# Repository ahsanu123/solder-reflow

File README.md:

<h1 align="center">🌕 SORE V3 - Prototype 1</h1> 
<p align="center">
  
</p>

<p align="center">

</p>

## ✏️ SORE - Solder Reflow

🌕 SORE - Solder Reflow,  DIY hot plate use PT100 for temperature sensor controlled with ESP32-S3,
with TFT LCD, programmed in 🦀 Rust with [Slint](https://slint.dev/) as user interface

> Designed With [KICAD](https://www.kicad.org)

## 🏆 WIP For Version 3

> [!NOTE]
> - use esp32-s3
> - use usb jtag and usb serial 
> - try to use power supply module instead of using external adaptor, [Hi-Link](https://www.tokopedia.com/eltech-online/hi-link-3-3v-5v-9v-12v-24v-hi-link-ling-hlk-ac-to-dc-isolation-power-supply-unit-switching-module-catu-daya-adaptor-trafo-all-1731008119444047082?extParam=ivf%3Dfalse%26keyword%3Dpower+supply+ac+dc%26search_id%3D20250611123128432ACA3A1E345E32EJ1R%26src%3Dsearch)
> - add generic lcd spi connector instead of spesific display pinout.
> - use [Slint](https://slint.dev/) for user interface
> - think about how to stack the heater so its not separated, model it with inventor
> - if possible, buy local component only

<details>
 <summary>Sketch</summary>
  
</details>
 
## 🖍️ Plot of Sampled Data

<details>
 <summary>
  Plot Collection
 </summary>
 
- multiple sampling at 2Mhz (except first one)
signal was moving averaged filter, first graph was actually noisy, and rest was actually not really noisy, but after filtered low noise signal look bumped

- Transfer Function Estimation
$`y(t) = 350(1-e^{(t-d)/tau})`$ in temperature degre (celcius), d = 17.5 second

- first time sampled diagram [30 oktober 2024]

</details>

## 🌱 V3 Project Progress

<details>
 <summary>
  Expand To See Progress.
 </summary> 
  
 **Version 2**
- PCB Design Finished 10 june 2024 20:51
- Order _BOM_ and PCB
- PCB and BOM Arrive 12 july 2024 about 16:00
- Start to soldering 13 july 2024 about 06:00 (**weekend**)
- make adc class to simplify adc initialization 23 july 2024 at 21:21
- Check Out GPIO (Worked!!😃) 26 july 2024 at 22:24
- Try to use JLink for jtag debugging, but fail 😞 , 27 july 2024 at 17:30
- Try again to use JLink for jtag debugging, Worked!! 😃 , 28 july 2024 at 11:36
- Add `Button` class to add Input with callback, 29 Agustus 2024 at 19:42
- ⚠️ turn out, TL074 (not TL074xH) need minimum 10v to operate and not single supply quad opamp 😞, fortunately there is LM324 (same package and single supply support), currently still in shipping, need to wait if it really work or not, 01 september 2024 at 18:05
- ✔️ ok LM324 worked, currently still investigate why adc are really noisy, 03 september 2024 at 13:34
- looks ESP32 IDF adc getting more stable if `frequency` increased, try to use 20Khz but its not stable, but use 1Mhz its more stable 14 september 2024 at 21:00
- ✔️ LVGL worked but task semaphore block update of LVGL (still investigate), 05 oktober 2024 at 10:13
- ✔️ now LVGL with Button input worked!! 😃, need learn more how to map LVGL key to input button, 05 oktober 2024 at 13:23
- ✔️ sampling data from heater and plot it, 30 oktober 2024 at 2015

**Version 3**
- ⏰ 11 June 2025 19:31, make it version 3,
- ⏰ 14 September 2025 12:57, complete basic pcb component placement.
- ⏰ 14 September 2025 17:59, after searching for **Random turn on SSR** (non Zero Crossing) on local market, i cant find easy to buy device, so i will stick to use zero crossing ssr and will count for zero crossing with **H11AA1** and determine how long to turn on and turn off.

- ⏰ 15 March 2026, able to run slint on ESP32S3 on `temperature-measurement-dongle`

</details>

## 🌴 Reference 

- Slint on Mcu platform sample docs -> https://github.com/slint-ui/slint/blob/master/examples/mcu-board-support/README.md
- Slint MCU support Discussion -> https://github.com/slint-ui/slint/discussions/5008
- Slint MCU Template (raspi pico) -> https://github.com/slint-ui/slint-mcu-rust-template/blob/main/src/main.rs
- Slint Linux Template (Linux, etc) -> https://github.com/slint-ui/slint-rust-template/tree/main
- Slint ESP32 Example -> https://github.com/slint-ui/slint/blob/master/examples/mcu-board-support/esp32_s3_box_3.rs
- SSR Phidgets -> https://www.phidgets.com/docs/Solid_State_Relay_Guide?srsltid=AfmBOorYCC74pJUGRt7l37kUGJY9RvW-y3PI6dPv29tLXrCDrbclxS5B

<sup> Work In Progress Version 3 for 2025 🔥, Made with ♥️ by AH... </sup>

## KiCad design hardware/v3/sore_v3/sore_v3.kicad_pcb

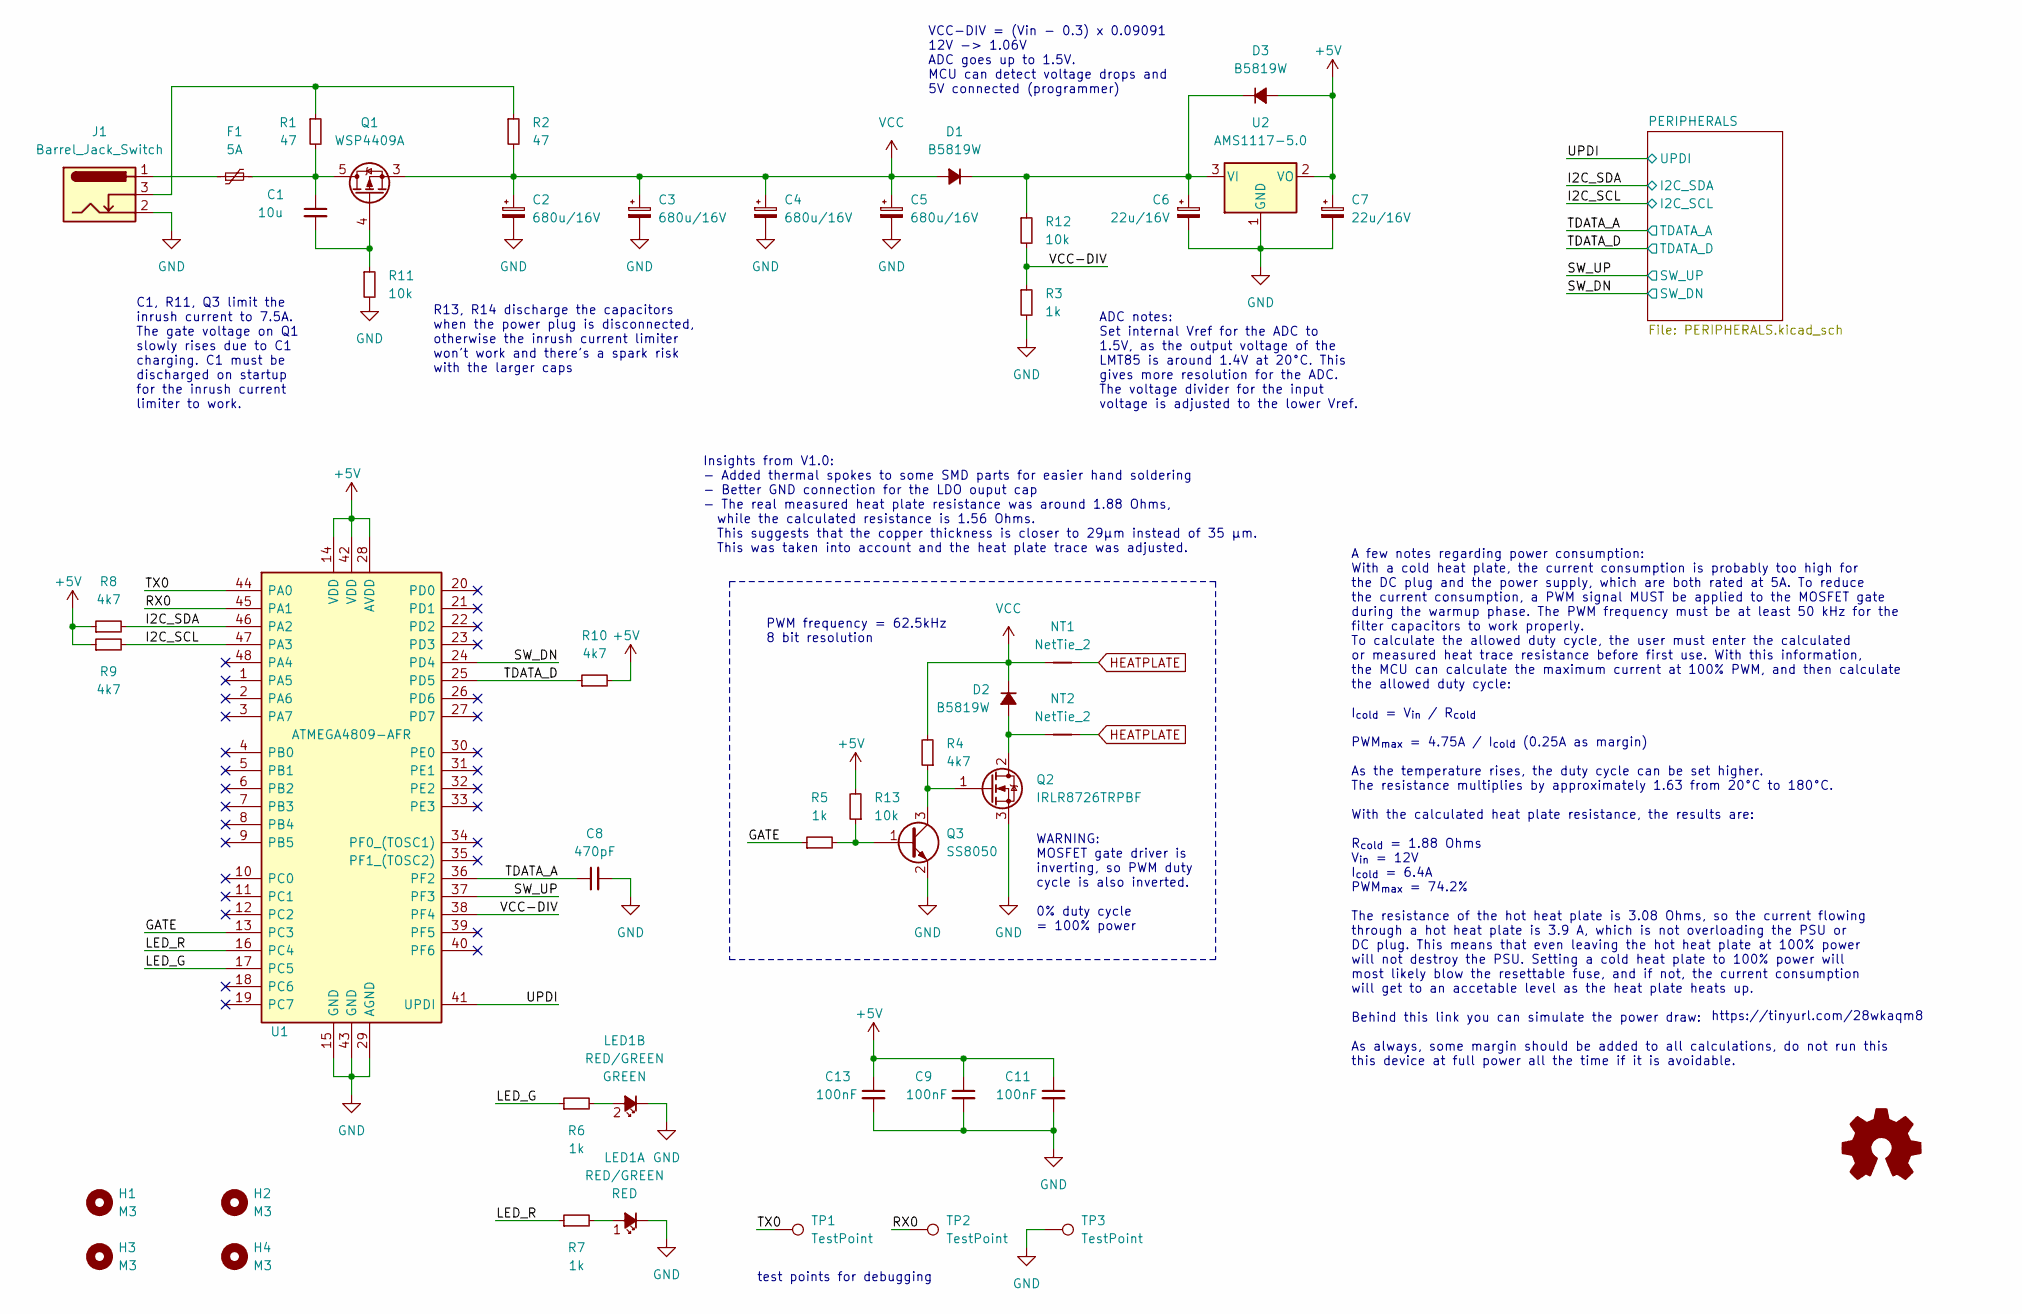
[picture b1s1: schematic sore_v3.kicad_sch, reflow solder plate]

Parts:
C1: 10u; C_0805_2012Metric; LCSC Part Number C2922480
C2, C3, C4, C5: 680u/16V; CP_Radial_D8.0mm_P3.50mm; LCSC Part Number C88760
C6, C7: 22u/16V; CP_Elec_4x5.4; LCSC Part Number C88799
C8: 470pF; C_0805_2012Metric; LCSC Part Number C1743
C9, C11, C13: 100nF; C_0805_2012Metric; LCSC Part Number C1711
D1, D2, D3: B5819W; D_SOD-123; LCSC Part Number C64885
F1: 5A; Fuse_2920_7451Metric; LCSC Part Number C910846
H1, H2, H3, H4: M3; MountingHole_3.2mm_M3; LCSC Part Number C551332
J1: Barrel_Jack_Switch; BarrelJack_Horizontal; LCSC Part Number C381115
LED1: RED/GREEN; LED_Avago_PLCC4_3.2x2.8mm_CW; LCSC Part Number C131251
LOGO1: Logo_Open_Hardware_Small; OSHW-Logo2_7.3x6mm_SilkScreen
NT1, NT2: NetTie_2; NetTie-2_SMD_Pad1.3mm
Q1: WSP4409A; SOIC-8_3.9x4.9mm_P1.27mm; LCSC Part Number C2880527
Q2: IRLR8726TRPBF; TO-252-2; LCSC Part Number C81137
Q3: SS8050; SOT-23; LCSC Part Number C444722
R1, R2: 47; R_0805_2012Metric; LCSC Part Number C17714
R3, R5, R6, R7: 1k; R_0805_2012Metric; LCSC Part Number C17513
R4, R8, R9, R10: 4k7; R_0805_2012Metric; LCSC Part Number C17673
R11, R12, R13: 10k; R_0805_2012Metric; LCSC Part Number C17414
TP1, TP2, TP3: TestPoint; TestPoint_Pad_D1.5mm
U1: ATMEGA4809-AFR; TQFP-48_7x7mm_P0.5mm; Manufacturer_Part_Number ATMEGA4809-AFR; Mouser Part Number 556-ATMEGA4809-AFR
U2: AMS1117-5.0; SOT-89-3; LCSC Part Number C351450

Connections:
+5V: C7.1, C9.1, C11.1, C13.1, D3.2 (A), R8.1, R9.1, R10.2, R13.2, U1.14 (VDD), U1.28 (AVDD), U1.42 (VDD), U2.2 (VO); also elsewhere on the board
/GATE: R5.1, U1.13 (PC3)
/I2C_SCL: R9.2, U1.47 (PA3); also elsewhere on the board
/I2C_SDA: R8.2, U1.46 (PA2); also elsewhere on the board
/LED_G: R6.1, U1.17 (PC5)
/LED_R: R7.1, U1.16 (PC4)
/RX0: TP2.1, U1.45 (PA1)
/SW_DN: U1.24 (PD4); also elsewhere on the board
/SW_UP: U1.37 (PF3); also elsewhere on the board
/TDATA_A: C8.1, U1.36 (PF2); also elsewhere on the board
/TDATA_D: R10.1, U1.25 (PD5); also elsewhere on the board
/TX0: TP1.1, U1.44 (PA0)
/UPDI: U1.41 (UPDI); also elsewhere on the board
/VCC-DIV: R3.1, R12.2, U1.38 (PF4)
GND: C2.2, C3.2, C4.2, C5.2, C6.2, C7.2, C8.2, C9.2, C11.2, C13.2, J1.2, LED1.2 (K1), LED1.4 (K2), Q2.3 (S), Q3.2 (E), R3.2, R11.2, TP3.1, U1.15 (GND), U1.29 (AGND), U1.43 (GND), U2.1 (GND); also elsewhere on the board
HEATPLATE: NT1.2, NT2.2
unnamed: C1.1, F1.2, Q1.5 (D), Q1.6 (D), Q1.7 (D), Q1.8 (D), R1.2
unnamed: C1.2, Q1.4 (G), R11.1
unnamed: C6.1, D1.1 (K), D3.1 (K), R12.1, U2.3 (VI)
unnamed: D2.2 (A), NT2.1, Q2.2 (D)
unnamed: F1.1, J1.1
unnamed: J1.3, R1.1, R2.1
unnamed: LED1.1 (A1), R7.2
unnamed: LED1.3 (A2), R6.2
unnamed: Q2.1 (G), Q3.3 (C), R4.1
unnamed: Q3.1 (B), R5.2, R13.1
VCC: C2.1, C3.1, C4.1, C5.1, D1.2 (A), D2.1 (K), NT1.1, Q1.1 (S), Q1.2 (S), Q1.3 (S), R2.2, R4.2

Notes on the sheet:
C1, R11, Q3 limit the inrush current to 7.5A. The gate voltage on Q1 slowly rises due to C1 charging. C1 must be discharged on startup for the inrush current limiter to work.
VCC-DIV = (Vin - 0.3) x 0.09091 12V -> 1.06V ADC goes up to 1.5V. MCU can detect voltage drops and 5V connected (programmer)
PWM frequency = 62.5kHz 8 bit resolution
A few notes regarding power consumption: With a cold heat plate, the current consumption is probably too high for the DC plug and the power supply, which are both rated at 5A. To reduce the current consumption, a PWM signal MUST be applied to the MOSFET gate during the warmup phase. The PWM frequen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
WARNING: MOSFET gate driver is inverting, so PWM duty cycle is also inverted. 0% duty cycle = 100% power
R13, R14 discharge the capacitors when the power plug is disconnected, otherwise the inrush current limiter won't work and there's a spark risk with the larger caps
https://tinyurl.com/28wkaqm8
test points for debugging
ADC notes: Set internal Vref for the ADC to 1.5V, as the output voltage of the LMT85 is around 1.4V at 20°C. This gives more resolution for the ADC. The voltage divider for the input voltage is adjusted to the lower Vref.
Insights from V1.0: - Added thermal spokes to some SMD parts for easier hand soldering - Better GND connection for the LDO ouput cap - The real measured heat plate resistance was around 1.88 Ohms, while the calculated resistance is 1.56 Ohms. This suggests that the copper thickness is closer to 29µ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

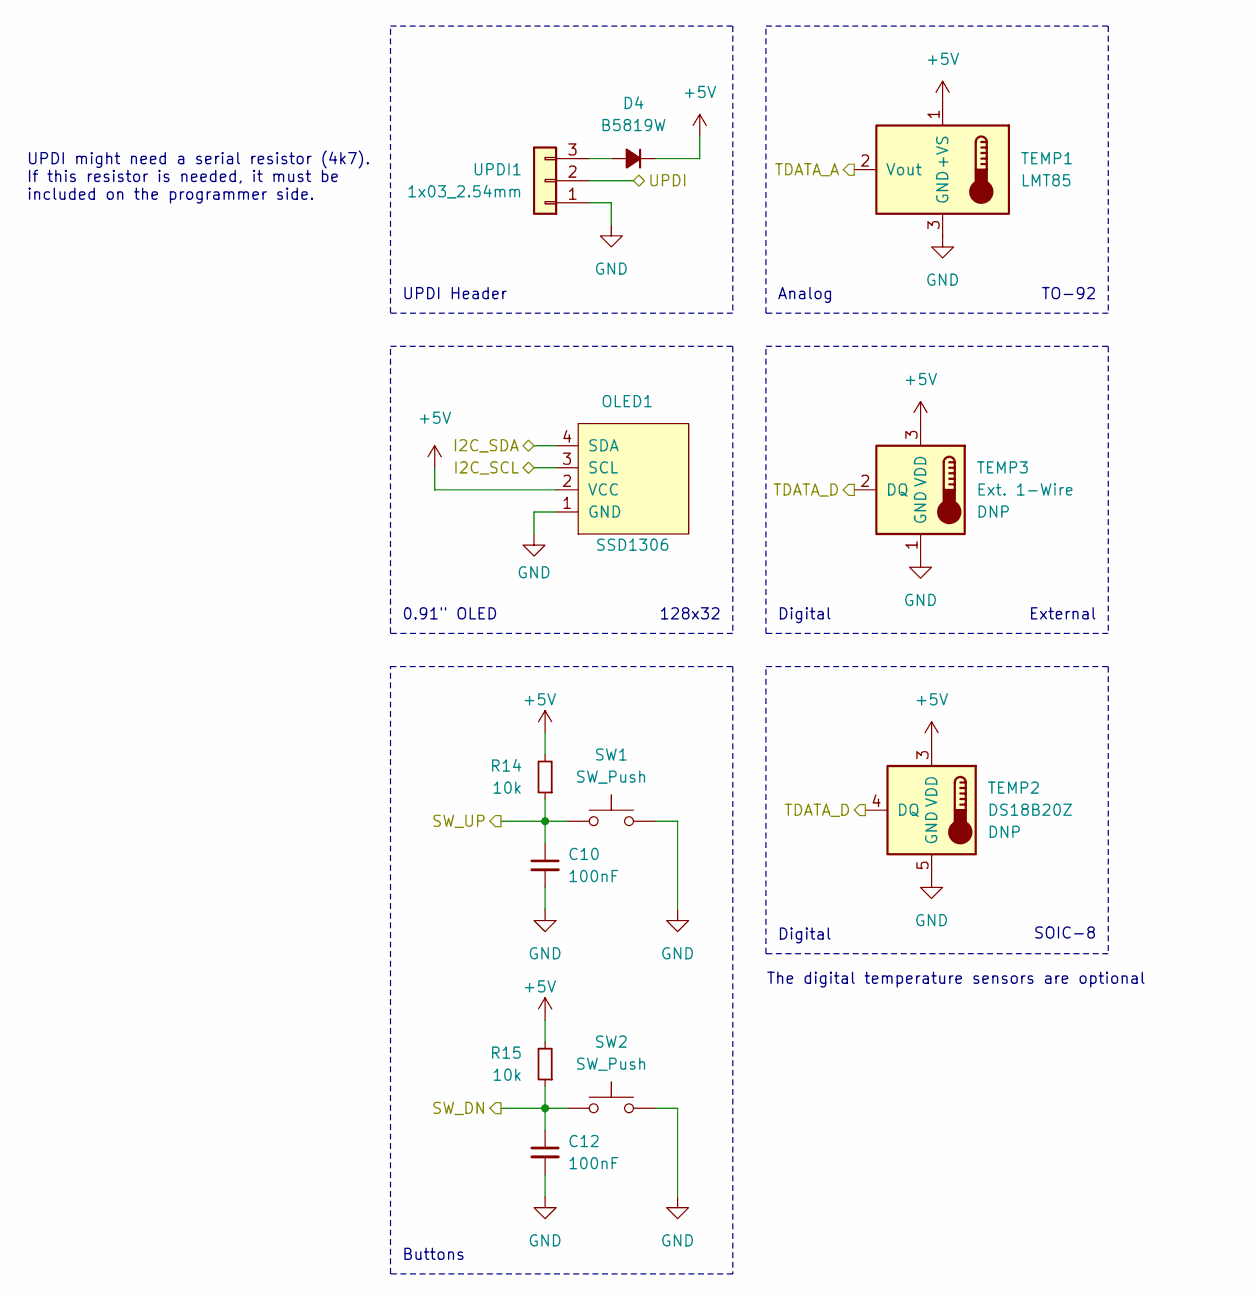
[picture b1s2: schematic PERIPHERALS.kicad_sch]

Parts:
C10, C12: 100nF; C_0805_2012Metric; LCSC Part Number C1711
D4: B5819W; D_SOD-123; LCSC Part Number C64885
OLED1: SSD1306; 0.91Inch-OLED-Module; LCSC Part Number C2718488
R14, R15: 10k; R_0805_2012Metric; LCSC Part Number C17414
SW1, SW2: SW_Push; SW_PUSH_6mm; LCSC Part Number C136682
TEMP1: LMT85; TO-92_Inline; LCSC Part Number C75856
TEMP2: DS18B20Z; SOIC-8_3.9x4.9mm_P1.27mm; LCSC Part Number C695837
TEMP3: Ext. 1-Wire; PinHeader_1x03_P2.54mm_Vertical
UPDI1: 1x03_2.54mm; PinHeader_1x03_P2.54mm_Vertical; LCSC Part Number C49257

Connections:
+5V: D4.1 (K), OLED1.2 (VCC), R14.2, R15.2, TEMP1.1 (+VS), TEMP2.3 (VDD), TEMP3.3 (VDD); also elsewhere on the board
/I2C_SCL: OLED1.3 (SCL); also elsewhere on the board
/I2C_SDA: OLED1.4 (SDA); also elsewhere on the board
/SW_DN: C12.1, R15.1, SW2.1; also elsewhere on the board
/SW_UP: C10.1, R14.1, SW1.1; also elsewhere on the board
/TDATA_A: TEMP1.2 (Vout); also elsewhere on the board
/TDATA_D: TEMP2.4 (DQ), TEMP3.2 (DQ); also elsewhere on the board
/UPDI: UPDI1.2; also elsewhere on the board
GND: C10.2, C12.2, OLED1.1 (GND), SW1.2, SW2.2, TEMP1.3 (GND), TEMP2.5 (GND), TEMP3.1 (GND), UPDI1.1; also elsewhere on the board
unnamed: D4.2 (A), UPDI1.3

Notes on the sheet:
SOIC-8
Digital
UPDI Header
128x32
Analog
TO-92
0.91" OLED
The digital temperature sensors are optional
Buttons
UPDI might need a serial resistor (4k7). If this resistor is needed, it must be included on the programmer side.
External

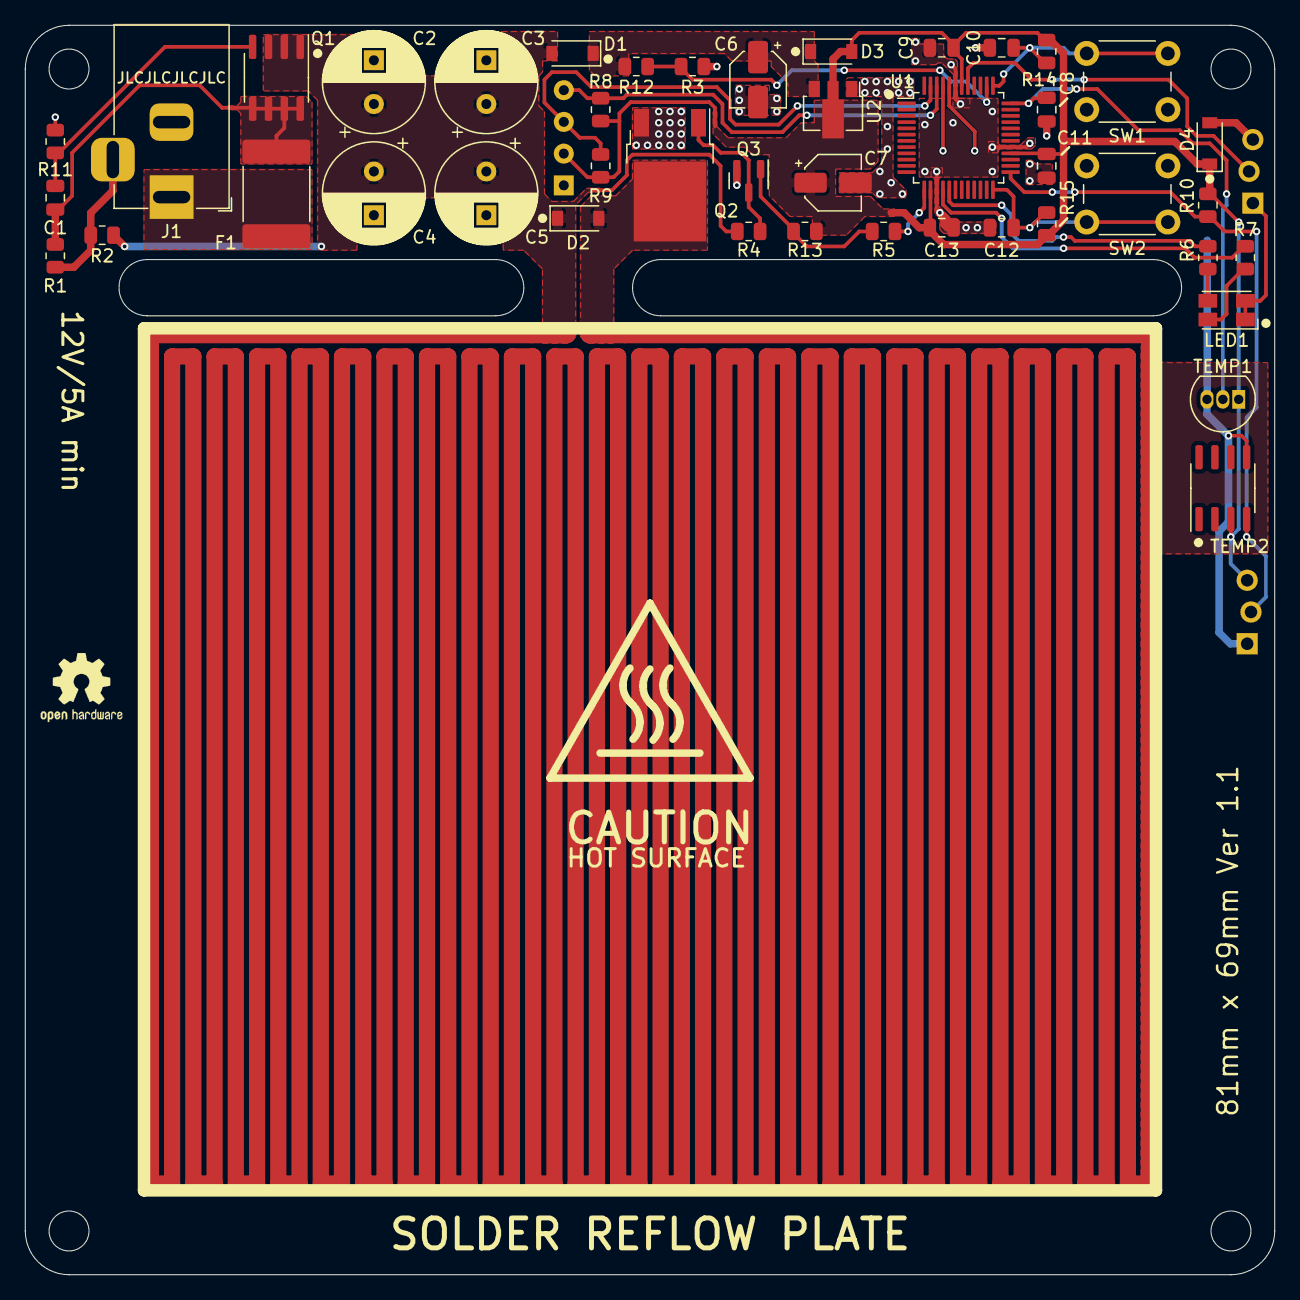
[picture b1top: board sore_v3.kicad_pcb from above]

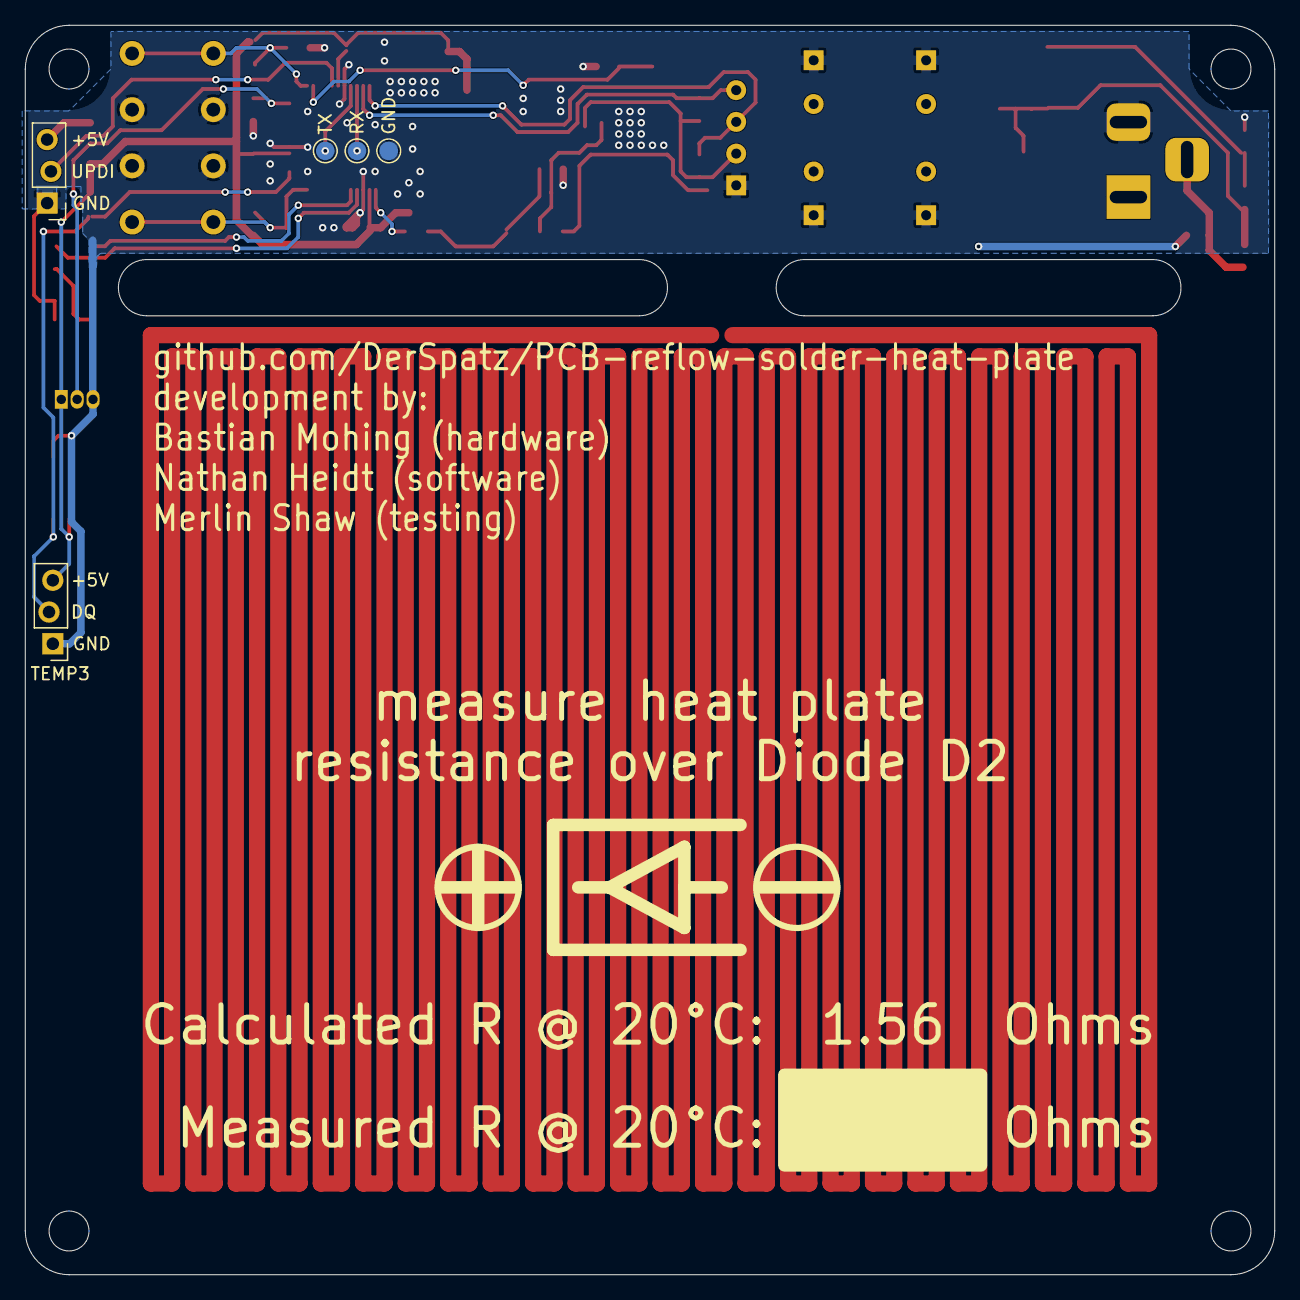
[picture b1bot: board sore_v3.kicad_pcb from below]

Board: 2 copper layers, 100.0 x 100.0 mm, 57 parts (5 on the bottom side), 28 nets.

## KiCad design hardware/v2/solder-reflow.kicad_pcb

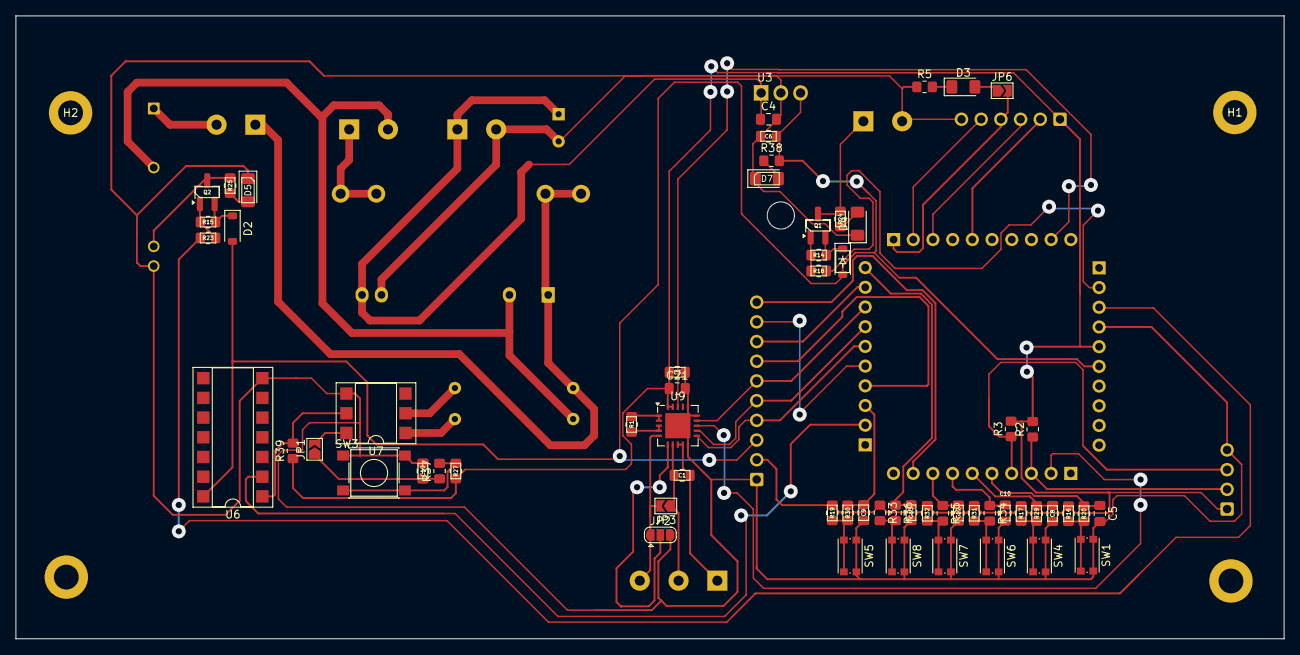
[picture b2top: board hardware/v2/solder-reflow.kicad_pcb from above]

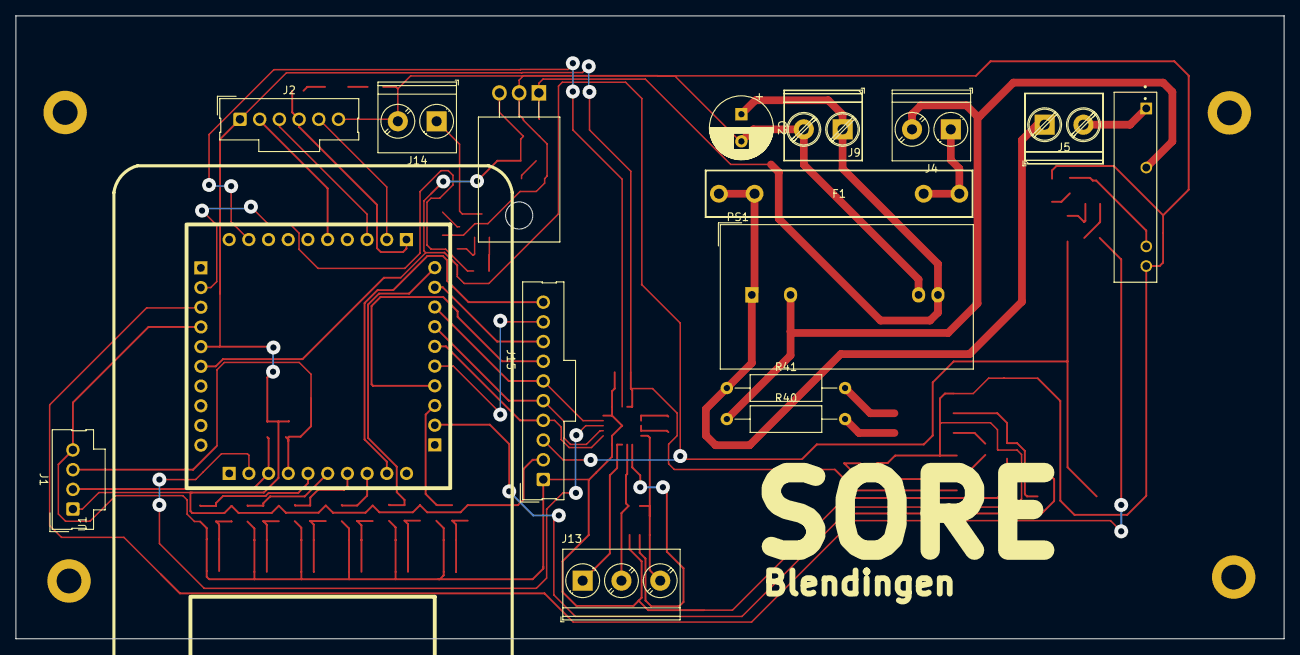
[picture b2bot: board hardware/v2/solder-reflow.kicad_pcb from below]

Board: 2 copper layers, 163.5 x 80.3 mm, 80 parts (16 on the bottom side), 61 nets.

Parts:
C1, C3, C21: 100nF; C_0805_2012Metric_Pad1.18x1.45mm_HandSolder
C2: 100uF/16V; CP_Radial_D8.0mm_P3.50mm
C4: 0.33uF; C_0805_2012Metric_Pad1.18x1.45mm_HandSolder
C5, C8, C9, C10, C12, C13, C19: 1uF; C_0805_2012Metric_Pad1.18x1.45mm_HandSolder
C6: 0.1uF; C_0805_2012Metric_Pad1.18x1.45mm_HandSolder
D1, D2: 1N4001; D_SOD-123
D3: Indicator; LED_1206_3216Metric_Pad1.42x1.75mm_HandSolder
D4: SSR2; LED_1206_3216Metric_Pad1.42x1.75mm_HandSolder
D5: SSR1; LED_1206_3216Metric_Pad1.42x1.75mm_HandSolder
D7: POWER_LED; LED_1206_3216Metric_Pad1.42x1.75mm_HandSolder
F1: Fuse; Fuseholder_Littelfuse_100_series_5x30mm
H1, H2, H3, H4: MountingHole_Pad; MountingHole_3.2mm_M3_DIN965_Pad
J1: I2C; Molex_SL_171971-0004_1x04_P2.54mm_Vertical
J2: I2S; Molex_SL_171971-0006_1x06_P2.54mm_Vertical
J4: 220V; TerminalBlock_Phoenix_PT-1,5-2-5.0-H_1x02_P5.00mm_Horizontal
J5: HEATER; TerminalBlock_Phoenix_PT-1,5-2-5.0-H_1x02_P5.00mm_Horizontal
J9: 12VIN; TerminalBlock_Phoenix_PT-1,5-2-5.0-H_1x02_P5.00mm_Horizontal
J13: RTD_PT100; TerminalBlock_Phoenix_PT-1,5-3-5.0-H_1x03_P5.00mm_Horizontal
J14: SSROUT2; TerminalBlock_Phoenix_PT-1,5-2-5.0-H_1x02_P5.00mm_Horizontal
J15: LCD_CONN; Molex_SL_171971-0010_1x10_P2.54mm_Vertical
JP1: InH11AA1; SolderJumper-2_P1.3mm_Open_TrianglePad1.0x1.5mm
JP2: 3_OR_2_Wire; SolderJumper-3_P1.3mm_Open_RoundedPad1.0x1.5mm
JP3, JP6: 2_Wire; SolderJumper-2_P1.3mm_Open_TrianglePad1.0x1.5mm
K1: G3MB202PDC12; RELAY_G3MB202PDC12
PS1: HLK-2M12 12V 2W; Converter_ACDC_Hi-Link_HLK-2Mxx
Q1, Q2: SS8550; SOT-23_Handsoldering
R1: 400 1%; R_0805_2012Metric_Pad1.20x1.40mm_HandSolder
R2, R3: 4K7; R_0805_2012Metric_Pad1.20x1.40mm_HandSolder
R5: 1K; R_0805_2012Metric_Pad1.20x1.40mm_HandSolder
R14, R15, R16, R17, R18, R19, R23, R27, R31, R32, R33, R39: 10k; R_0805_2012Metric_Pad1.20x1.40mm_HandSolder
R20, R29, R30, R34, R35, R36, R37: 22k; R_0805_2012Metric_Pad1.20x1.40mm_HandSolder
R24, R25, R38: 1k; R_0805_2012Metric_Pad1.20x1.40mm_HandSolder
R40, R41: 10k 1W; R_Axial_DIN0309_L9.0mm_D3.2mm_P15.24mm_Horizontal
SW1: L; SW_Push_1P1T_NO_CK_KMR2
SW3: SWH11AA1; SW_Push_1P1T_NO_6x6mm_H9.5mm
SW4: D; SW_Push_1P1T_NO_CK_KMR2
SW5: U; SW_Push_1P1T_NO_CK_KMR2
SW6, SW7, SW8: R; SW_Push_1P1T_NO_CK_KMR2
U1: ESP32-S3-Tempel; esp32-s3-tempel
U3: L7805; TO-220F-3_Horizontal_TabDown
U6: 74LS14; DIP-14_W7.62mm_SMDSocket_SmallPads
U7: H11AA1; DIP-6_W7.62mm_SMDSocket_SmallPads
U9: MAX31865xTP; TQFN-20-1EP_5x5mm_P0.65mm_EP3.25x3.25mm

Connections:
+3.3V: C3.1, C21.1, J1.1, J2.1, J15.2, R2.2, R3.2, R16.1, R17.1, R19.1, R27.1, R31.1, R32.1, R33.1, R39.1, U1.35 (3V3), U9.19 (DVDD), U9.20 (VDD)
+5V: C6.1, D1.2 (A), D2.2 (A), J15.3, R38.2, U1.36 (5V), U3.3 (OUT), U6.14 (VCC)
+12V: C2.1, C4.1, J9.1, PS1.4 (+Vout), U3.1 (IN)
/BCLK: J2.3, U1.23 (IO45)
/CS0: J15.9, U1.15 (IO10)
/DIO: J2.5, U1.22 (IO48)
/I2C_SCL: J1.3, R3.1, U1.4 (IO7)
/I2C_SDA: J1.2, R2.1, U1.3 (IO6)
/IN1: C5.1, R20.1, U1.5 (IO15)
/IN2: C8.1, R29.1, U1.6 (IO16)
/IN3: C9.1, R30.1, U1.13 (IO46)
/IN4: C10.1, R34.1, U1.7 (IO17)
/IN5: C12.1, R35.1, U1.8 (IO18)
/IN6: C13.1, R36.1, U1.20 (IO21)
/IO5: U1.2 (IO5), U9.13 (~CS)
/IO8: J15.10, U1.9 (IO8)
/IO42: U1.29 (IO42), U9.18 (~DRDY)
/MCLK: J2.2, U1.25 (IO38)
/MISO: J15.6, U1.18 (IO13), U9.14 (SDO)
/MOSI: J15.4, U1.16 (IO11), U9.11 (SDI)
/QUADHD: J15.7, U1.14 (IO9)
/QUADWP: J15.8, U1.19 (IO14)
/SCLK: J15.5, U1.17 (IO12), U9.12 (SCLK)
/SSRIN1: R23.1, U1.33 (IO1)
/SSRIN2: R18.1, U1.32 (IO2)
/WS: J2.4, JP6.2 (B), U1.21 (IO47)
/ZC_INPUT: U1.12 (IO3), U6.2
/sw1: R16.2, R20.2, SW1.2
/sw2: R17.2, R29.2, SW4.2
/sw3: R19.2, R30.2, SW5.2
/sw4: R31.2, R34.2, SW6.2
/sw5: R32.2, R35.2, SW7.2
/sw6: R33.2, R36.2, SW8.2
GND: C2.2, C3.2, C4.2, C5.2, C6.2, C8.2, C9.2, C10.2, C12.2, C13.2, C19.2, C21.2, D4.1 (K), D5.1 (K), D7.1 (K), J1.4, J2.6, J9.2, J14.2, J15.1, JP2.3 (B), K1.4 (-), PS1.3 (-Vout), R5.1, SW1.1, SW3.1, SW4.1, SW5.1, SW6.1, SW7.1, SW8.1, U1.34 (GND), U3.2 (GND), U6.7 (GND), U7.4, U9.10 (GND), U9.15 (DGND), U9.16 (GND), U9.21 (GND)
LINE: F1.1, J5.1, PS1.1 (AC/L), R41.1
NEUT: J4.2, K1.2 (L2), PS1.2 (AC/N), R40.1
unnamed: D1.1 (K), Q1.2 (E), R14.2
unnamed: D2.1 (K), Q2.2 (E), R15.2
unnamed: D3.2 (A), JP6.1 (A)
unnamed: D3.1 (K), R5.2
unnamed: D4.2 (A), R24.1
unnamed: D5.2 (A), R25.1
unnamed: D7.2 (A), R38.1
unnamed: F1.2, J4.1
unnamed: J5.2, K1.1 (L1)
unnamed: C1.2, J13.1, U9.8 (RTDIN-), U9.9 (FORCE-)
unnamed: C1.1, J13.2, JP3.1 (A), U9.7 (RTDIN+)
unnamed: J13.3, JP2.1 (A), JP3.2 (B), U9.5 (FORCE+)
unnamed: J14.1, Q1.3 (C), R24.2
unnamed: C19.1, JP1.1 (A), R37.1
unnamed: JP1.2 (B), U7.6
unnamed: JP2.2 (C), U9.6 (FORCE2)
unnamed: K1.3 (+), Q2.3 (C), R25.2
unnamed: Q1.1 (B), R14.1, R18.2
unnamed: Q2.1 (B), R15.1, R23.2
unnamed: R27.2, R37.2, SW3.2
unnamed: R39.2, U6.1, U7.5
unnamed: R40.2, U7.1
unnamed: R41.2, U7.2
unnamed: R1.1, U9.1 (BIAS), U9.2 (REFIN+)
unnamed: R1.2, U9.3 (REFIN-), U9.4 (ISENSOR)
